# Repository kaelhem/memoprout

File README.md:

# MemoProut Connect

[Check it out](https://memoprout-pad-connect.web.app/)

This web app is a work in progress that will allow MemoProut Pad owners to :
+ Update the firmware (_Chrome only_)
+ Add / remove game modes (_Chrome only_)
+ Create and share new game modes

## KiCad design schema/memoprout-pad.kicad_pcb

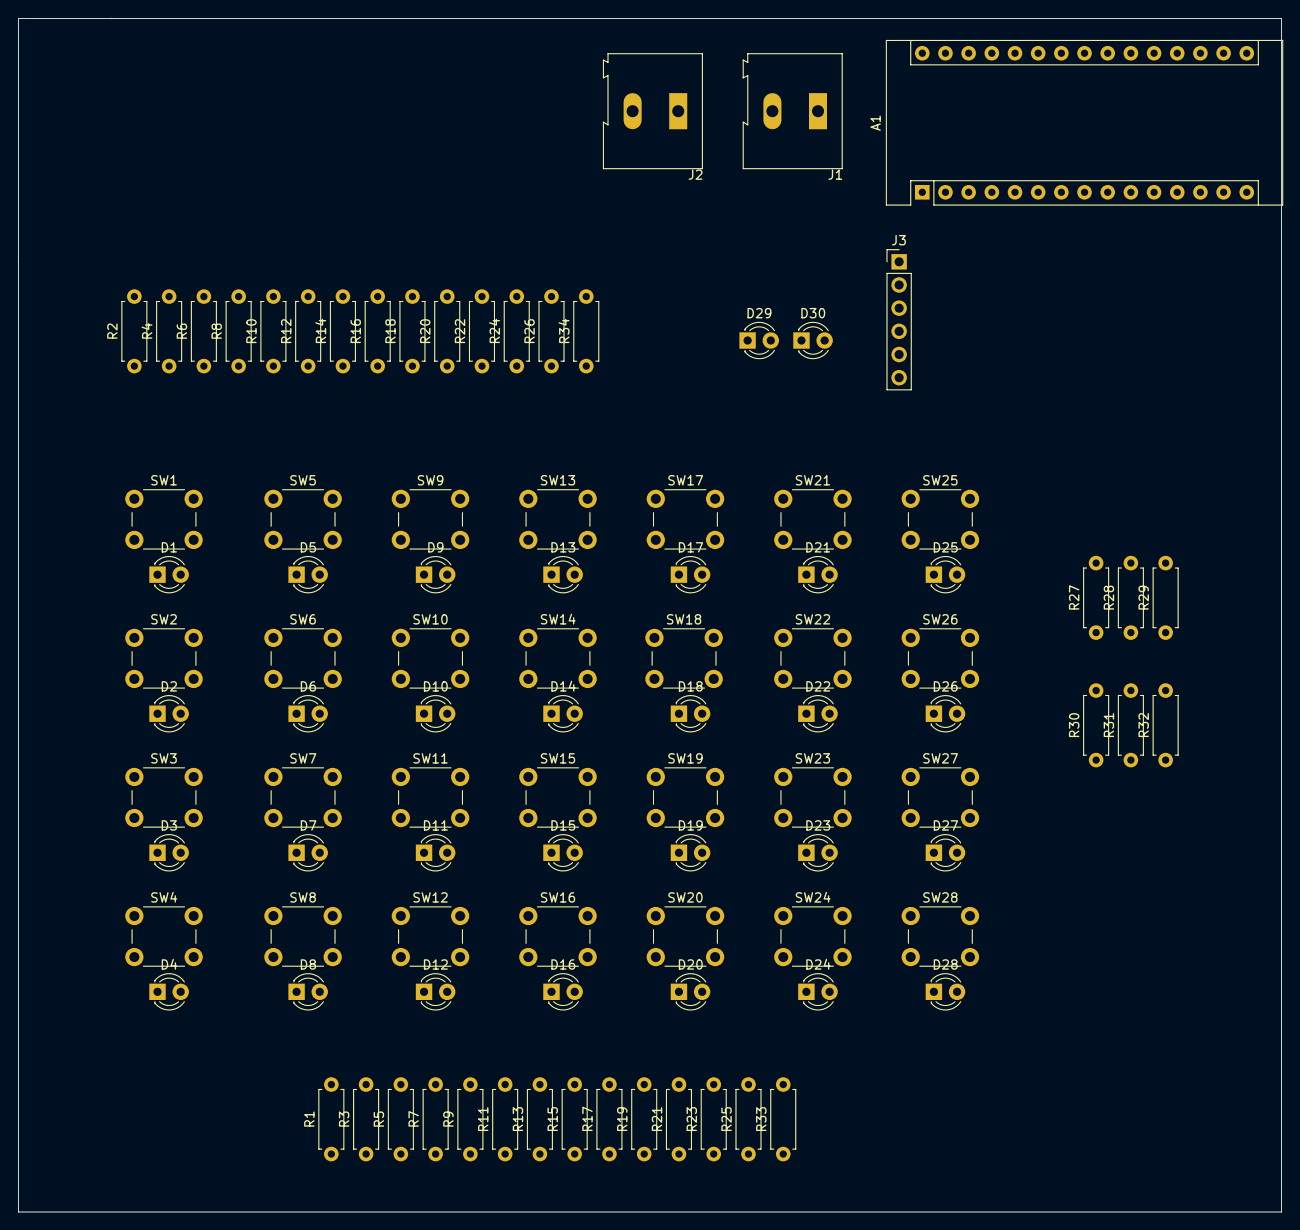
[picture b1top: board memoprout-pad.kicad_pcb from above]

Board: 2 copper layers, 138.4 x 130.8 mm, 96 parts (0 on the bottom side), 72 nets, no tracks yet.

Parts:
A1: Arduino_Nano_v3.x; Arduino_Nano
D1, D2, D3, D4, D5, D6, D7, D8, D9, D10, D11, D12, D13, D14, D15, D16, D17, D18, D19, D20, D21, D22, D23, D24, D25, D26, D27, D28, D29, D30: LED; LED_D3.0mm
J1: POWER; TerminalBlock_Altech_AK300-2_P5.00mm
J2: SPEAKER; TerminalBlock_Altech_AK300-2_P5.00mm
J3: SD CARD; PinHeader_1x06_P2.54mm_Vertical
R1, R2: 10KΩ; R_Axial_DIN0207_L6.3mm_D2.5mm_P7.62mm_Horizontal
R3, R4: 3.3KΩ; R_Axial_DIN0207_L6.3mm_D2.5mm_P7.62mm_Horizontal
R5, R6: 1.8KΩ; R_Axial_DIN0207_L6.3mm_D2.5mm_P7.62mm_Horizontal
R7, R8: 1KΩ; R_Axial_DIN0207_L6.3mm_D2.5mm_P7.62mm_Horizontal
R9, R10: 680Ω; R_Axial_DIN0207_L6.3mm_D2.5mm_P7.62mm_Horizontal
R11, R12: 560Ω; R_Axial_DIN0207_L6.3mm_D2.5mm_P7.62mm_Horizontal
R13, R14, R15, R16: 330Ω; R_Axial_DIN0207_L6.3mm_D2.5mm_P7.62mm_Horizontal
R17, R18: 220Ω; R_Axial_DIN0207_L6.3mm_D2.5mm_P7.62mm_Horizontal
R19, R20, R21, R22: 180Ω; R_Axial_DIN0207_L6.3mm_D2.5mm_P7.62mm_Horizontal
R23, R24, R25, R26, R32: 120Ω; R_Axial_DIN0207_L6.3mm_D2.5mm_P7.62mm_Horizontal
R27, R28, R29, R30, R31: R; R_Axial_DIN0207_L6.3mm_D2.5mm_P7.62mm_Horizontal
R33, R34: 1.5KΩ; R_Axial_DIN0207_L6.3mm_D2.5mm_P7.62mm_Horizontal
SW1, SW2, SW3, SW4, SW5, SW6, SW7, SW8, SW9, SW10, SW11, SW12, SW13, SW14, SW15, SW16, SW17, SW18, SW19, SW20, SW21, SW22, SW23, SW24, SW25, SW26, SW27, SW28: BT0; SW_PUSH_6mm_H4.3mm_4Pins

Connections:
+5V: A1.27, J3.2, R33.1, R34.1
/D9: A1.12, J2.2
/GND: A1.4, J1.2, J2.1, J3.1, SW25.4, SW26.4, SW27.4, SW28.4
/VIN: A1.30, J1.1
BT_1: A1.20, R26.1, R34.2, SW25.1
BT_2: R24.1, R26.2, SW21.1
BT_3: R22.1, R24.2, SW17.1
BT_4: R20.1, R22.2, SW13.1
BT_5: R18.1, R20.2, SW9.1
BT_6: R16.1, R18.2, SW5.1
BT_7: R14.1, R16.2, SW1.1
BT_8: R12.1, R14.2, SW26.1
BT_9: R10.1, R12.2, SW22.1
BT_10: R8.1, R10.2, SW18.1
BT_11: R6.1, R8.2, SW14.1
BT_12: R4.1, R6.2, SW10.1
BT_13: R2.1, R4.2, SW6.1
BT_14: R2.2, SW2.1
BT_15: A1.21, R25.1, R33.2, SW27.1
BT_16: R23.1, R25.2, SW23.1
BT_17: R21.1, R23.2, SW19.1
BT_18: R19.1, R21.2, SW15.1
BT_19: R17.1, R19.2, SW11.1
BT_20: R15.1, R17.2, SW7.1
BT_21: R13.1, R15.2, SW3.1
BT_22: R11.1, R13.2, SW28.1
BT_23: R9.1, R11.2, SW24.1
BT_24: R7.1, R9.2, SW20.1
BT_25: R5.1, R7.2, SW16.1
BT_26: R3.1, R5.2, SW12.1
BT_27: R1.1, R3.2, SW8.1
BT_28: R1.2, SW4.1
CS: A1.13, J3.3
LED_1: D3.1, D4.1, D7.2, D8.2, D11.1, D12.1, D15.2, D16.2, D20.1, D24.2, R27.1
LED_2: D2.1, D4.2, D6.2, D8.1, D10.1, D14.2, D19.1, D23.2, D27.1, D28.2, R28.1
LED_3: D1.1, D5.2, D9.1, D12.2, D13.2, D16.1, D18.1, D19.2, D22.2, D23.1, R29.1
LED_4: D17.1, D18.2, D20.2, D21.2, D22.1, D24.1, D25.1, D26.2, D27.2, D28.1, R30.1
LED_5: D1.2, D2.2, D3.2, D5.1, D6.1, D7.1, D17.2, D21.1, D29.2, D30.1, R31.1
LED_6: D9.2, D10.2, D11.2, D13.1, D14.1, D15.1, D25.2, D26.1, D29.1, D30.2, R32.1
MISO: A1.15, J3.5
MOSI: A1.14, J3.4
unnamed: A1.5, R27.2
unnamed: A1.6, R28.2
unnamed: A1.7, R29.2
unnamed: A1.8, R30.2
unnamed: A1.9, R31.2
unnamed: A1.10, R32.2
unnamed: SW1.4, SW5.3
unnamed: SW2.4, SW6.3
unnamed: SW3.4, SW7.3
unnamed: SW4.4, SW8.3
unnamed: SW5.4, SW9.3
unnamed: SW6.4, SW10.3
unnamed: SW10.4, SW14.3
unnamed: SW7.4, SW11.3
unnamed: SW11.4, SW15.3
unnamed: SW8.4, SW12.3
unnamed: SW12.4, SW16.3
unnamed: SW9.4, SW13.3
unnamed: SW13.4, SW17.3
unnamed: SW14.4, SW18.3
unnamed: SW15.4, SW19.3
unnamed: SW16.4, SW20.3
unnamed: SW17.4, SW21.3
unnamed: SW18.4, SW22.3
unnamed: SW19.4, SW23.3
unnamed: SW20.4, SW24.3
unnamed: SW21.4, SW25.3
unnamed: SW22.4, SW26.3
unnamed: SW23.4, SW27.3
unnamed: SW24.4, SW28.3
SCK: A1.16, J3.6

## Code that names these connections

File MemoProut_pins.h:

/*
  MemoProut_pins.h - Defines the pins for the Memoprout Pad©
  Created by klem on 06/11/2019
*/
#ifndef MemoProut_pins_h
#define MemoProut_pins_h

// PINS FOR LEDS (charlieplexing)
#define LED_1 2
#define LED_2 3
#define LED_3 4
#define LED_4 5
#define LED_5 6
#define LED_6 7

// PINS (analog) FOR ForteenButtons connectors
#define PIN_BUTTONS_TOP 1
#define PIN_BUTTONS_BOTTOM 2

// PIN for SD card
#define SD_PIN 10

// PIN for speaker
#define SPEAKER_PIN 9

// Buttons identifier
#define BT_1 0
#define BT_2 2
#define BT_3 4
#define BT_4 6
#define BT_5 8
#define BT_6 10
#define BT_7 12
#define BT_8 1
#define BT_9 3
#define BT_10 5
#define BT_11 7
#define BT_12 9
#define BT_13 11
#define BT_14 13
#define BT_15 15
#define BT_16 17
#define BT_17 19
#define BT_18 21
#define BT_19 23
#define BT_20 25
#define BT_21 27
#define BT_22 14
#define BT_23 16
#define BT_24 18
#define BT_25 20
#define BT_26 22
#define BT_27 24
#define BT_28 26

#endif

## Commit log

2019-11-07 memoprout-pad first commit
2019-11-07 a bit of code cleaning
2019-11-07 it starts to works :sparkles:
2019-11-08 added ui sounds
2019-11-08 added small optim with avr/pgmspace
2019-11-08 added read/write hiscore
2019-11-13 use external tool to generates random games abd load them from sd card
2019-11-13 added kicad files, sd card data and generator tool
2019-11-13 fixed game generator + normalize all sounds + added volume in config file
2019-11-14 added mutli-touch actions to manage volume in game
2019-11-14 added some sounds (cinema)
2019-11-14 added music game kind
2019-11-15 allow to play smoothly by skipping current playing sound
2019-11-15 first commit of the website
2019-11-15 fix mobile rendering
2019-11-15 wip on website
2019-11-15 small css improvements
2019-11-16 added contact form
2019-11-16 added feedback on contact form
2019-11-16 fix mail data name
2019-11-16 do not send contact while input fields are empty
2019-11-17 added some entries into the faq
2019-11-17 typos
2019-11-17 improve description, removed © everywhere
2019-11-17 added burger-menu for mobiles
2019-11-18 removed readme
2019-11-18 added readme
2019-11-18 added license
2019-11-18 added user guide
2019-11-18 mv png logo
2019-11-18 updated user guide
2019-11-18 updated content + added icons
2019-11-18 fix license link
2019-11-21 optimisations, clean repo, added ordimini contrib
2019-11-21 wording
2019-11-21 added user-guide in pdf + renamed things
2019-11-22 added memoprout.svg file
2019-12-03 update arduino code to match pcb scheme + wip on memoprout-connect
2019-12-05 updated stl button model
2019-12-05 moved mpp-connect into its own branch
2019-12-05 create mpp-connect branch
2019-12-07 manage firebase auth
2019-12-07 fix icon color in footer
2019-12-13 added 3D models + updated firmware
2019-12-13 added stickers
2019-12-13 wording update
2019-12-16 added new game mode + fixed some sounds
2019-12-16 added doc for new game modes
2019-12-16 faq update
2019-12-16 fix link
2019-12-16 updated pictures
2019-12-17 added device connect / disconnect
2019-12-17 added disclaimer and some css
2019-12-18 :tada: flashing firmware is working (ATMega only)
2019-12-18 wip on install / uninstall games
2019-12-18 added link to mmp-connect into faq
2019-12-19 wip on file upload... not very lucky until now
2019-12-19 updated faq
2019-12-19 added version / wip on file upload
2019-12-19 deactivated games install/uninstall...
2019-12-20 remove link to mpp-connect
2019-12-20 added link to user guide
2020-05-29 added open graph meta data
